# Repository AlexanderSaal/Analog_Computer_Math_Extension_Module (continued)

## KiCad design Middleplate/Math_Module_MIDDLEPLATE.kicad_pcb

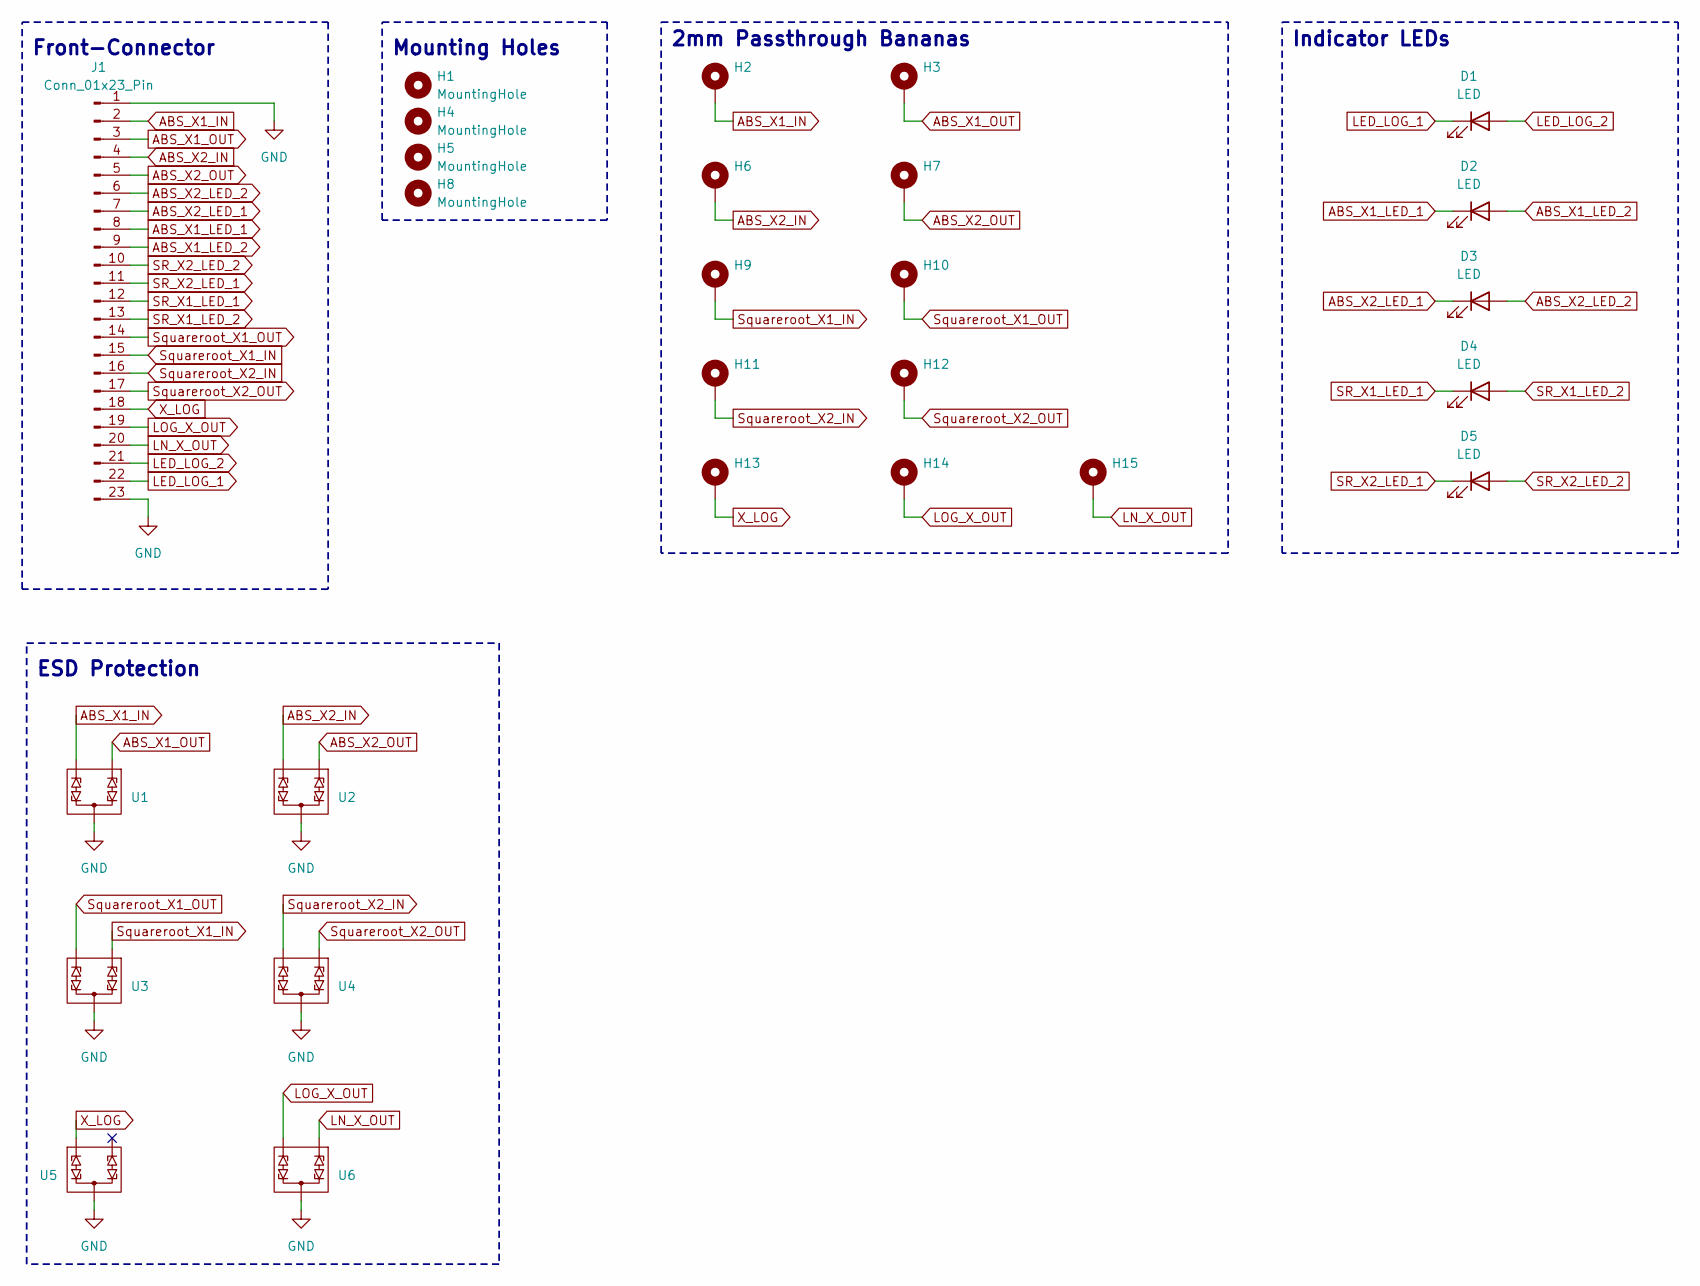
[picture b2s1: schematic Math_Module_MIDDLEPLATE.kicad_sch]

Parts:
D1, D2, D3, D4, D5: LED; LED_D3.0mm_FlatTop
H1, H4, H5, H8: MountingHole; MountingHole_3.2mm_M3_DIN965
H2: ABS_X1_IN; MountingHole_4.3mm_M4_DIN965_Pad
H3: ABS_X1_OUT; MountingHole_4.3mm_M4_DIN965_Pad
H6: ABS_X2_IN; MountingHole_4.3mm_M4_DIN965_Pad
H7: ABS_X2_OUT; MountingHole_4.3mm_M4_DIN965_Pad
H9: Squareroot_X1_IN; MountingHole_4.3mm_M4_DIN965_Pad
H10: Squareroot_X1_OUT; MountingHole_4.3mm_M4_DIN965_Pad
H11: Squareroot_X2_IN; MountingHole_4.3mm_M4_DIN965_Pad
H12: Squareroot_X2_OUT; MountingHole_4.3mm_M4_DIN965_Pad
H13: X_LOG_IN; MountingHole_4.3mm_M4_DIN965_Pad
H14: LOG_X_OUT; MountingHole_4.3mm_M4_DIN965_Pad
H15: LN_X_OUT; MountingHole_4.3mm_M4_DIN965_Pad
J1: Conn_01x23_Pin; PinSocket_1x23_P2.54mm_Vertical
U1, U2, U3, U4, U5, U6: VCAN16A2; VCAN16A2-03S-E3-08

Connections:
ABS_X1_IN: H2.1, J1.2, U1.2 (IN2)
ABS_X1_LED_1: D2.1 (K), J1.8
ABS_X1_LED_2: D2.2 (A), J1.9
ABS_X1_OUT: H3.1, J1.3, U1.1 (IN1)
ABS_X2_IN: H6.1, J1.4, U2.2 (IN2)
ABS_X2_LED_1: D3.1 (K), J1.7
ABS_X2_LED_2: D3.2 (A), J1.6
ABS_X2_OUT: H7.1, J1.5, U2.1 (IN1)
GND: J1.1, J1.23, U1.3 (OUT), U2.3 (OUT), U3.3 (OUT), U4.3 (OUT), U5.3 (OUT), U6.3 (OUT)
LED_LOG_1: D1.1 (K), J1.22
LED_LOG_2: D1.2 (A), J1.21
LN_X_OUT: H15.1, J1.20, U6.1 (IN1)
LOG_X_OUT: H14.1, J1.19, U6.2 (IN2)
SR_X1_LED_1: D4.1 (K), J1.12
SR_X1_LED_2: D4.2 (A), J1.13
SR_X2_LED_1: D5.1 (K), J1.11
SR_X2_LED_2: D5.2 (A), J1.10
Squareroot_X1_IN: H9.1, J1.15, U3.1 (IN1)
Squareroot_X1_OUT: H10.1, J1.14, U3.2 (IN2)
Squareroot_X2_IN: H11.1, J1.16, U4.2 (IN2)
Squareroot_X2_OUT: H12.1, J1.17, U4.1 (IN1)
X_LOG: H13.1, J1.18, U5.1 (IN1)

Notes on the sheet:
2mm Passthrough Bananas
Front-Connector
ESD Protection
Indicator LEDs
Mounting Holes

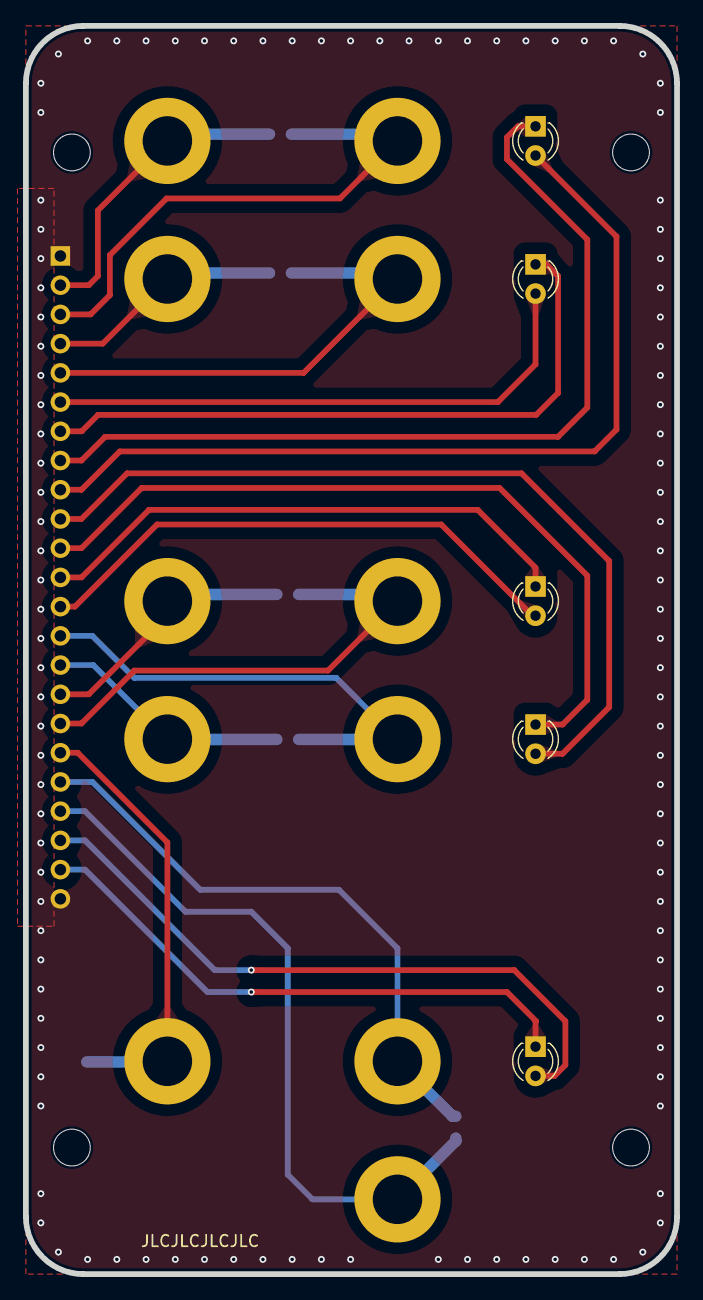
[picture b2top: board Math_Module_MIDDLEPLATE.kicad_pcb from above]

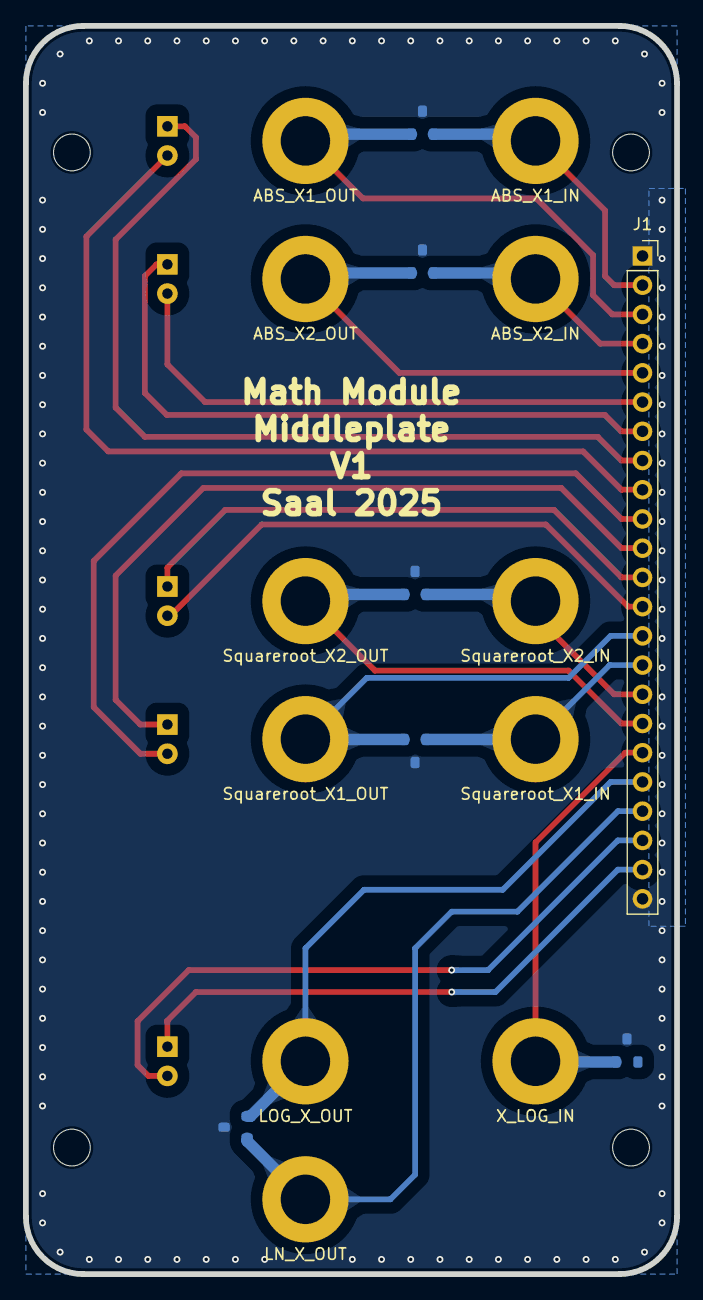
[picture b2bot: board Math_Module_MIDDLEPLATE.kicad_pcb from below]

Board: 2 copper layers, 56.6 x 108.5 mm, 27 parts (18 on the bottom side), 22 nets.

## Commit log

2025-02-13 V1 finished
